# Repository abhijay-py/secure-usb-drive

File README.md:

# secure-usb-drive
Our device has a fixed number of four users. When the user enters the correct password on the keypad or enters the correct fingerprint, they get to access the files corresponding to their user. <br>

Initially, all the users’ passwords are four zeros. When the user plugs in the USB drive, the LCD screen says, "Select User" and they must enter a number on the keypad to select the user (1 for user one, 2 for user two, 3 for user three, and 4 for user four). Then the LCD screen shows “Enter Passcode / Fingerprint” and the screen displays what the user types on the keypad. As the user types, their input is replaced with a dot. Once the user enters the correct passcode or inputs the correct fingerprint, the USB drive goes into the unlocked state where all the files for that user can be accessed. Each user gets their own designated flash chip. In the unlocked state, the user can press a button on the keypad to change the passcode or change the fingerprint and can press another button to lock the USB drive.<br>

The system is implemented using an STM32 microcontroller. It handles interfacing with the keypad, LCD screen, fingerprint sensor, four flash chips, and a host computer. It also handles keeping track of what state it’s in and handles keeping track of what user is accessing the flash drive. The system is powered through the 5V USB signal that is interfaced with the 5V USB-A female connector. According to the USB 2.0 specifications, it can handle an input voltage ranging from 4.75V to 5.25V. This input voltage directly powers the LCD screen. There is a low dropout regulator to step down the voltage to 3.3V to power the microcontroller, fingerprint sensor, and the flash chips.The system is enclosed in a 3D-printed rectangular case. Since the user must press down on the USB drive to enter a password, it can be connected to a computer using a cable instead of directly into a computer. <br>

All documentation, PCB, schematic, CAD, and software files can be found in their respective folders. <br>

The embedded code can be flashed onto the product by utilizing STM32CubeIDE and connecting an ST-Link and the five header pins on the PCB. The PCB is attached to the casing utilizing two screws on the inside and the casing is closed up with four screws. The connectors on the board will need to be attached to the LCD, fingerprint sensor, and keypad from the outside of the casing after feeding the connecting wires through the holes on the casing. <br><br>
 <br><br>

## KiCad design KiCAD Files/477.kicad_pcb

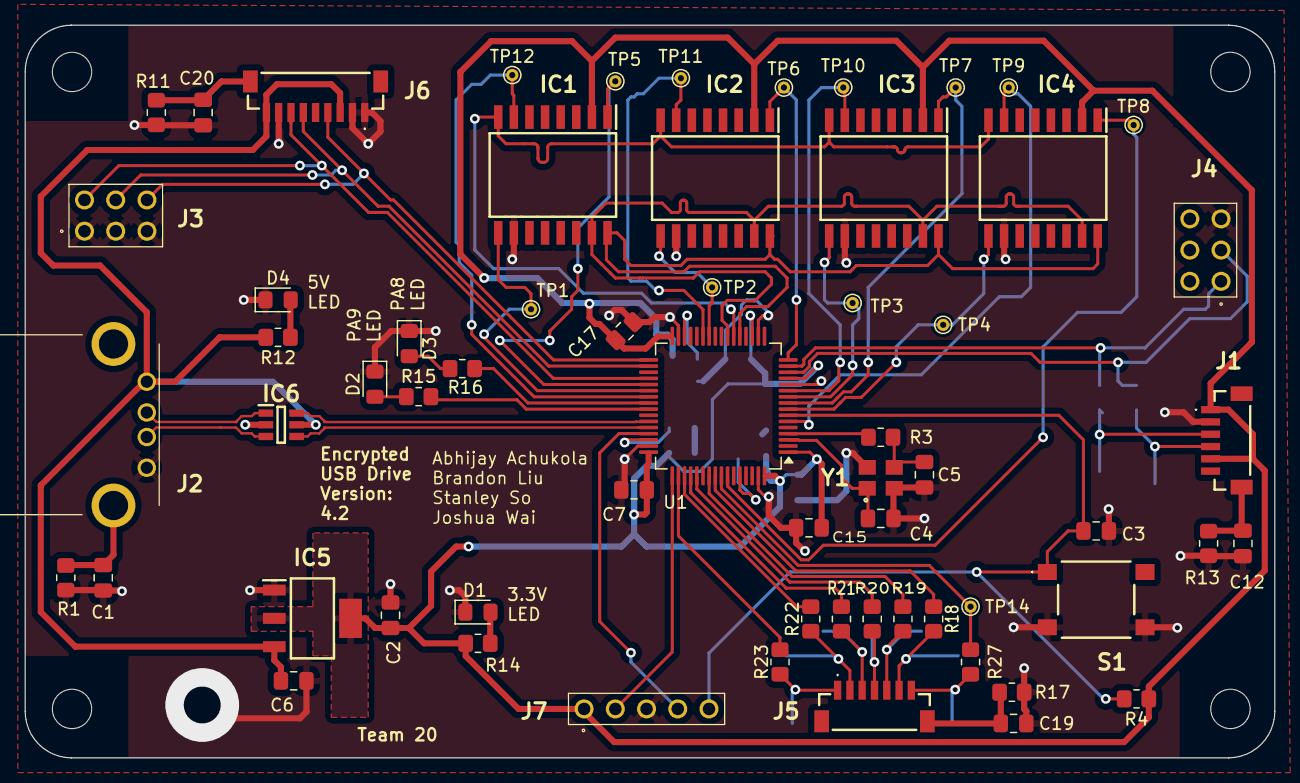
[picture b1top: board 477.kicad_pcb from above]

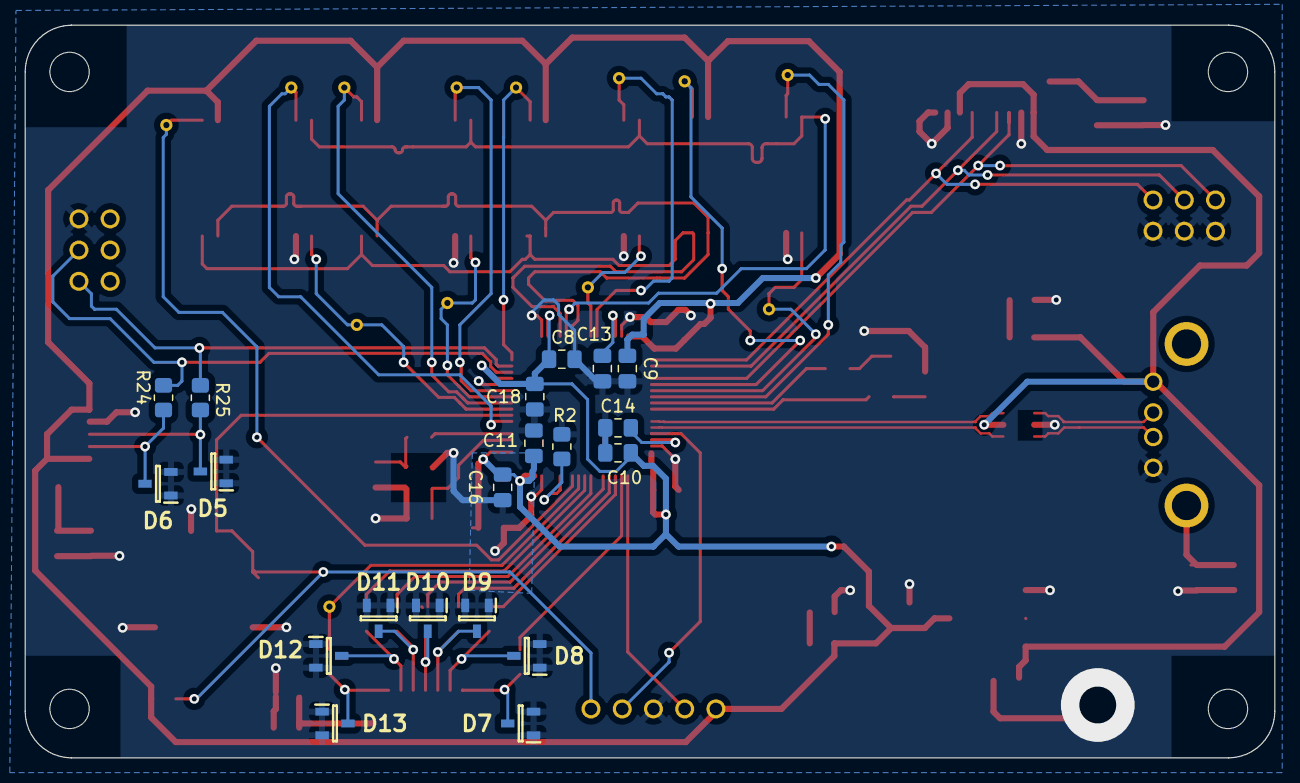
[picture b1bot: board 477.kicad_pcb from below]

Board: 2 copper layers, 101.7 x 59.6 mm, 86 parts (20 on the bottom side), 62 nets.

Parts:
C1, C12, C19, C20: 2.2n; C_0805_2012Metric_Pad1.18x1.45mm_HandSolder
C2: 22u; C_0805_2012Metric_Pad1.18x1.45mm_HandSolder
C3: 0.1u; C_0805_2012Metric_Pad1.18x1.45mm_HandSolder
C4, C5: 10p; C_0805_2012Metric_Pad1.18x1.45mm_HandSolder
C6: 10u; C_0805_2012Metric_Pad1.18x1.45mm_HandSolder
C7: 4.7u; C_0805_2012Metric_Pad1.18x1.45mm_HandSolder
C8, C9, C10, C11, C13, C14, C16, C18: 100n; C_0805_2012Metric_Pad1.18x1.45mm_HandSolder
C15, C17: 1u; C_0805_2012Metric_Pad1.18x1.45mm_HandSolder
D1, D2, D3, D4: LED; LED_0805_2012Metric_Pad1.15x1.40mm_HandSolder
D5, D6, D7, D8, D9, D10, D11, D12, D13: D5V0L2B3SO-7; SOT96P240X110-3N
H1, H2, H3, H4: MountingHole; MountingHole_3.2mm_M3_DIN965
IC1, IC2, IC3, IC4: W25N01GVSFIG; SOIC127P1032X264-16N
IC5: AZ1117IH-3.3TRG1; SOT230P700X180-4N
IC6: USBLC6-2SC6; SOT95P280X145-6N
J1: BM06B-SRSS-TBT_LF__SN_; BM06BSRSSTBTLFSN
J2: 6364372-2; 63643722
J3, J4: TSW-103-14-S-D; custom1
J5: BM07B-SRSS-TB_LF__SN_; BM07BSRSSTBLFSN
J6: BM09B-SRSS-TB_LF__SN_; BM09BSRSSTBLFSN
J7: TSW-105-05-F-S; TSW-105-XX-YY-S
R1, R11, R13, R17: 1M; R_0805_2012Metric_Pad1.20x1.40mm_HandSolder
R2: 10k; R_0805_2012Metric_Pad1.20x1.40mm_HandSolder
R3: 330; R_0805_2012Metric_Pad1.20x1.40mm_HandSolder
R4: 1K; R_0805_2012Metric_Pad1.20x1.40mm_HandSolder
R12, R14, R15, R16, R24, R25: 220; R_0805_2012Metric_Pad1.20x1.40mm_HandSolder
R18, R19, R20, R21, R22, R23, R27: 1000; R_0805_2012Metric_Pad1.20x1.40mm_HandSolder
S1: 222AMVBAR; custom
TP1, TP2, TP3, TP4, TP5, TP6, TP7, TP8, TP9, TP10, TP11, TP12, TP14: TestPoint; TestPoint_THTPad_D1.0mm_Drill0.5mm
U1: STM32H7A3RGTx; LQFP-64_10x10mm_P0.5mm
Y1: ABM8G-48.000MHZ-18-D2Y-T; ABM8G

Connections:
+5V: C6.1, IC5.3 (INPUT), IC6.5 (VBUS), J2.1, J6.3, J6.9, R12.2
/Microcontroller Circuitry/BOOT0: R2.1, U1.60 (BOOT0)
D+: IC6.3 (I/O2_1), J2.3
D-: IC6.1 (I/O1_1), J2.2
FP RX: D5.3, J1.3, R25.1
FP TX: D6.3, J1.4, R24.1
GND: C1.2, C2.2, C3.2, C4.2, C5.2, C6.2, C7.2, C8.2, C9.2, C10.2, C11.2, C12.2, C13.2, C14.2, C15.2, C16.2, C17.2, C18.2, C19.2, C20.2, D1.1 (K), D2.1 (K), D3.1 (K), D4.1 (K), D5.1, D5.2, D6.1, D6.2, D7.1, D7.2, D8.1, D8.2, D9.1, D9.2, D10.1, D10.2, D11.1, D11.2, D12.1, D12.2, D13.1, D13.2, IC1.10 (GND), IC2.10 (GND), IC3.10 (GND), IC4.10 (GND), IC5.1 (ADJ/GND), IC6.2 (GND), J1.2, J2.4, J3.1, J3.3, J3.5, J4.5, J6.1, J6.2, J6.8, J7.3, R1.2, R2.2, R11.2, R13.2, R17.2, S1.2 (NO_1), S1.4 (NO_2), U1.12 (VSSA), U1.18 (VSS), U1.31 (VSS), U1.47 (VSS), U1.63 (VSS), Y1.2 (GND_1), Y1.4 (GND_2)
KeyC1: D7.3, J5.1, R23.1
KeyC2: D8.3, J5.2, R22.1
KeyC3: D9.3, J5.3, R21.1
KeyR1: D10.3, J5.4, R20.1
KeyR2: D11.3, J5.5, R19.1
KeyR3: D12.3, J5.6, R18.1
KeyR4: D13.3, J5.7, R27.1
unnamed: C1.1, J2.MH2, R1.1
unnamed: C12.1, J1.MP2, R13.1
unnamed: C19.1, J5.MP2, R17.1
unnamed: C20.1, J6.MP2, R11.1
unnamed: D1.2 (A), R14.1
unnamed: D2.2 (A), R15.1
unnamed: D3.2 (A), R16.1
unnamed: D4.2 (A), R12.1
unnamed: C5.1, R3.1, Y1.3 (XTAL_2)
PA0/FP TX ESD: J4.3, R24.2, U1.14 (PA0)
PA1/FP RX ESD: J4.1, R25.2, U1.15 (PA1)
PA2/HOLD2: IC2.1 (/HOLD_(IO3)), TP6.1, U1.16 (PA2)
PA5/SCK: IC1.16 (CLK), IC2.16 (CLK), IC3.16 (CLK), IC4.16 (CLK), U1.21 (PA5)
PA6/MISO: IC1.8 (DO_(IO1_)), IC2.8 (DO_(IO1_)), IC3.8 (DO_(IO1_)), IC4.8 (DO_(IO1_)), U1.22 (PA6)
PA7/MOSI: IC1.15 (DI_(IO0_)), IC2.15 (DI_(IO0_)), IC3.15 (DI_(IO0_)), IC4.15 (DI_(IO0_)), U1.23 (PA7)
PA8/Debug: R16.2, U1.40 (PA8)
PA9/Debug: R15.2, U1.41 (PA9)
PA13/SWDIO: J7.4, U1.45 (PA13)
PA14/SWCLK: J7.2, U1.49 (PA14)
PA15/KeyC1 ESD: R23.2, U1.50 (PA15)
PB0/WP2: IC2.9 (/WP_(IO2_)), TP2.1, U1.26 (PB0)
PB1/CS2: IC2.7 (/CS), TP11.1, U1.27 (PB1)
PB3/KeyR2 ESD: R19.2, U1.55 (PB3)
PB4/KeyR3 ESD: R18.2, U1.56 (PB4)
PB5/KeyR4 ESD: R27.2, TP14.1, U1.57 (PB5)
PB6/HOLD4: IC4.1 (/HOLD_(IO3)), TP8.1, U1.58 (PB6)
PB12/LCD NSS: J3.6, J6.4, U1.33 (PB12)
PB13/LCD SCK: J3.4, J6.6, U1.34 (PB13)
PB15/LCD MOSI: J3.2, J6.7, U1.36 (PB15)
PC0/WP4: IC4.9 (/WP_(IO2_)), TP4.1, U1.8 (PC0)
PC1/HOLD3: IC3.1 (/HOLD_(IO3)), TP7.1, U1.9 (PC1)
PC2/WP3: IC3.9 (/WP_(IO2_)), TP3.1, U1.10 (PC2)
PC3/CS3: IC3.7 (/CS), TP10.1, U1.11 (PC3)
PC6/HOLD1: IC1.1 (/HOLD_(IO3)), TP5.1, U1.37 (PC6)
PC7/WP1: IC1.9 (/WP_(IO2_)), TP1.1, U1.38 (PC7)
PC9/CS1: IC1.7 (/CS), TP12.1, U1.39 (PC9)
PC10/KeyC2 ESD: R22.2, U1.51 (PC10)
PC11/KeyC3 ESD: R21.2, U1.52 (PC11)
PC12/KeyR1 ESD: R20.2, U1.53 (PC12)
PC14/OSC IN: C4.1, U1.3 (PC14), Y1.1 (XTAL_1)
PC15/OSC OUT: R3.2, U1.4 (PC15)
PH1/CS4: IC4.7 (/CS), TP9.1, U1.6 (PH1)
USB+: IC6.4 (I/O2_2), U1.44 (PA12)
USB-: IC6.6 (I/O1_2), U1.43 (PA11)
VBAT: C2.1, C7.1, C8.1, C9.1, C10.1, C11.1, C15.1, C16.1, C17.1, C18.1, IC1.2 (VCC), IC2.2 (VCC), IC3.2 (VCC), IC4.2 (VCC), IC5.2 (OUTPUT), IC5.4 (VOUT), J1.1, J1.5, J7.1, R4.1, R14.2, U1.1 (VBAT), U1.13 (VDDA), U1.19 (VDD), U1.32 (VDD), U1.48 (VDD), U1.64 (VDD)
VCAP1: C13.1, U1.30 (VCAP)
VCAP2: C14.1, U1.46 (VCAP)
nRST: C3.1, J7.5, R4.2, S1.1 (COM_1), U1.7 (NRST)

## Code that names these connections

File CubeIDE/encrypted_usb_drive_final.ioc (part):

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Mcu.Name=STM32H7A3R(G-I)Tx
Mcu.Package=LQFP64
Mcu.UserName=STM32H7A3RGTx
PA0.Mode=Asynchronous
PA0.Signal=UART4_TX
PA1.Mode=Asynchronous
PA1.Signal=UART4_RX
PA11.Mode=Device_Only_FS
PA11.Signal=USB_OTG_HS_DM
PA12.Mode=Device_Only_FS
PA12.Signal=USB_OTG_HS_DP
PA13.Mode=Serial_Wire
PA13.Signal=DEBUG_JTMS-SWDIO
PA14.Mode=Serial_Wire
PA14.Signal=DEBUG_JTCK-SWCLK
PA15.GPIOParameters=GPIO_PuPd
PA15.GPIO_PuPd=GPIO_PULLDOWN
PA15.Signal=GPIO_Input
PA2.Signal=GPIO_Output
PA3.Signal=GPIO_Output
PA5.Mode=Full_Duplex_Master
PA5.Signal=SPI1_SCK
PA6.Mode=Full_Duplex_Master
PA6.Signal=SPI1_MISO
PA7.Mode=Full_Duplex_Master
PA7.Signal=SPI1_MOSI
PA8.Signal=GPIO_Output
PA9.Signal=GPIO_Output
PB0.Signal=GPIO_Output
PB1.Signal=GPIO_Output
PB12.Signal=GPIO_Output
PB13.Mode=TX_Only_Simplex_Unidirect_Master
PB13.Signal=SPI2_SCK
PB15.Mode=TX_Only_Simplex_Unidirect_Master
PB15.Signal=SPI2_MOSI
PB3.Signal=GPIO_Output
PB4.Signal=GPIO_Output
PB5.Signal=GPIO_Output
PB6.Signal=GPIO_Output
PC0.Signal=GPIO_Output
PC1.Signal=GPIO_Output
PC10.GPIOParameters=GPIO_PuPd
PC10.GPIO_PuPd=GPIO_PULLDOWN
PC10.Signal=GPIO_Input
PC11.GPIOParameters=GPIO_PuPd
PC11.GPIO_PuPd=GPIO_PULLDOWN
PC11.Signal=GPIO_Input
PC12.Signal=GPIO_Output
PC2.Signal=GPIO_Output
PC3.Signal=GPIO_Output
PC6.Signal=GPIO_Output
PC7.Signal=GPIO_Output
PC9.Signal=GPIO_Output
PH1-OSC_OUT.Signal=GPIO_Output
RCC.HSE_VALUE=24000000
RCC.SYSCLKFreq_VALUE=64000000
board=custom

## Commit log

2025-01-30 Added kicad files
2025-01-31 finished first draft of schematic
2025-02-10 got keypad code working
2025-02-12 checking kicad files
2025-02-12 Moved keypad code to new file
2025-02-12 finished keypad debouncing code
2025-02-12 finished keypad library code
2025-02-12 starting lcd code
2025-02-14 brought in stmf4xx hal driver for coding and spi testing
2025-02-15 started on flash ic functionality and reset command.
2025-02-18 MCU can communicate via SPI as the master - verified using oscilloscope
2025-02-18 got UART working
2025-02-18 wrote send_command function
2025-02-19 finished pcb draft
2025-02-19 wrote all fingerprint sensor TX code
2025-02-19 tweaked schematic
2025-02-24 LCD progress, can display some text on a different LCD
2025-02-24 lcd can display welcome message, clear, and turn off
2025-02-24 improved code quality of lcd.c
2025-02-25 wrote generate_package and receive_acknowledgment
2025-02-25 made all the commands send and receive
2025-02-25 disabled UART NVIC interrupt
2025-02-26 tweaked diagram and pin out setup.
2025-02-26 updating lcd branch before pulling flash ic branch
2025-02-26 updated schematic
2025-02-26 commiting pcb changes
2025-02-28 added button and tweaked silkscreen
2025-02-28 tweaked pcb and schematics with micro power wiring and debugging additions
2025-02-28 committing some unsaved changes
2025-02-28 tweaked schematic to pass erc
2025-03-01 added additional connector
2025-03-01 modified silkscreen
2025-03-01 found final connector
2025-03-01 finalized schematic
2025-03-02 modified mounting holes
2025-03-02 updated with 3d models
2025-03-03 added testing points
2025-03-05 routed essential signals
2025-03-05 Added the write_reg command
2025-03-05 Changed the code to the waveshare sensor
2025-03-05 MCU can retrieve jedec id from flash ic
2025-03-05 finished file
2025-03-05 fixed some routes, added more related to PC2, PC3, PC0, PA14, PA13, PC10, PD2, PB13
2025-03-05 Verified all the functions worked.
2025-03-06 Finalized Signal Routing
2025-03-06 finalized 99% of pcb
2025-03-07 updated files with 3d models
2025-03-07 finished schematic and pcb
2025-03-07 rounded edges
2025-03-07 updated pcb
2025-03-07 update 3d model
2025-03-07 rectangularized the pcb design.
2025-03-12 made most of the easy changes for the pcb
2025-03-12 cleaned up a bit of routing
2025-03-12 finalized pcb design (miso line is still cooked but better)
    finished up most of the pcb design work, need to check if we can route spi signals under the flash ic (or is it smth we look up in datasheet)?
2025-03-12 refilled ground plane to update to changes.
2025-03-12 okay final commit this time (gnd plane maximization)
2025-03-12 nvm added ground via to pass drc
2025-03-12 rerouted miso signals + minimized vias from top side by using test points as vias.
2025-03-12 brought power from outer layer to top layer
2025-03-12 fixed led acute angle traces
2025-03-12 tweaked silkscreen
2025-03-12 fixed weird routing
2025-03-12 made VBAT pad bigger
    hi Joshua
2025-03-12 added big ground pad that we can clip oscilloscope to
2025-03-14 added esd changes to schematic and pcb, mainly for J1 and J5, no DRC run
2025-03-14 Finished with changes to fix electric issues.
    power lines need to be relooked at
2025-03-14 testing github pages
2025-03-14 rerouted keypad
2025-03-14 finished PCB
2025-03-15 made a few tweaks based on setsuna's comments
2025-03-16 fixed DRC violation by connecting VBAT for C16
2025-03-16 previous edits may not be reflected, but they are now + no copper around oscillator
2025-03-16 added exclusion zone around oscillator
2025-03-16 recommitting, previous change may not be reflected
2025-03-16 added more exclusion zones around mounting holes
2025-03-16 recommitting because exclusion zone edits may not be saved
2025-03-16 added one giant ground plane on front and back and allowed stanley's VBAT zone to have higher priority to avoid DRC issues
2025-03-16 added pullup for nrst and fixed drc warnings for silkscreen
2025-03-18 uploaded tvs diode footprint and symbol
2025-03-18 fixed one acute angle and drc issue with ground plane on top layer
2025-03-18 changed ESD diode in schematic
2025-03-18 Routed new ESD diode
2025-03-18 created fabrication outputs
2025-03-24 tweaked 3d model characteristics to include diodes in 3d model
2025-04-07 updated project to h7
2025-04-07 updated with current flash ic prototyping
2025-04-07 removed old cubeide files
2025-04-07 finished status register
2025-04-07 added wen and wdisable function
2025-04-08 started on reading data
2025-04-08 Finished allowing reads.
2025-04-08 fixed reset issue and added lcd ic pin
2025-04-09 Started on writing data
2025-04-09 finished block erase and writes
    starting upper level funcs, maybe bbm
2025-04-09 Finalized core r/w functionality for flash ics
2025-04-14 Started usb and tweaked flash.c formatting to help usb interface
2025-04-14 adjusted spacing
2025-04-15 added read pin functionality
2025-04-16 finished intial function for USB reads
2025-04-16 updated keypad schematic
    rendered testpoint useless, but keypad should not require much use of test points.
2025-04-16 made writes + started fat32
2025-04-16 wrote testing code
2025-04-16 LCD PSDR checked off
2025-04-16 made keypad work
2025-04-18 replaced thumb drive with usb drive
2025-04-18 got basic USB communication to work, can send capacities but cannot store values once powered off in buffer
2025-04-18 can display custom lcd text
2025-04-23 added prospective LCD code for state machine
2025-04-24 changed to 512 sector size and ran into flash write errors
2025-04-24 wrote state machine
2025-04-24 I wrote some code to turn on LEDs
    for Brandon
2025-04-24 adding output and other files so that stanley can do work
2025-04-24 started debugging
2025-04-25 worked on state machine.
    List of things that don't work:
    - no distinct users (everyone shares the same keypad password)
    - changing fingerprint doesn't work
2025-04-25 added multiple users
2025-04-25 state machine works now
    actually stable commit
2025-04-25 made keypad inputs super fast
2025-04-25 changed back debounce value to lower
2025-04-25 finished flash
2025-04-25 remvoed debug files
2025-04-25 Finished flash IC stuff
2025-04-25 Final Code
2025-04-25 Fixed fingerprint
2025-04-25 adjusted key bouncing
2025-04-25 finalized code
2025-05-03 updated format and uploaded documents
2025-05-03 added a13
2025-05-03 removed temporary file
2025-05-11 revised readme for readibility and information
2025-06-19 added supporting images
2025-06-19 Update README.md with description and image
